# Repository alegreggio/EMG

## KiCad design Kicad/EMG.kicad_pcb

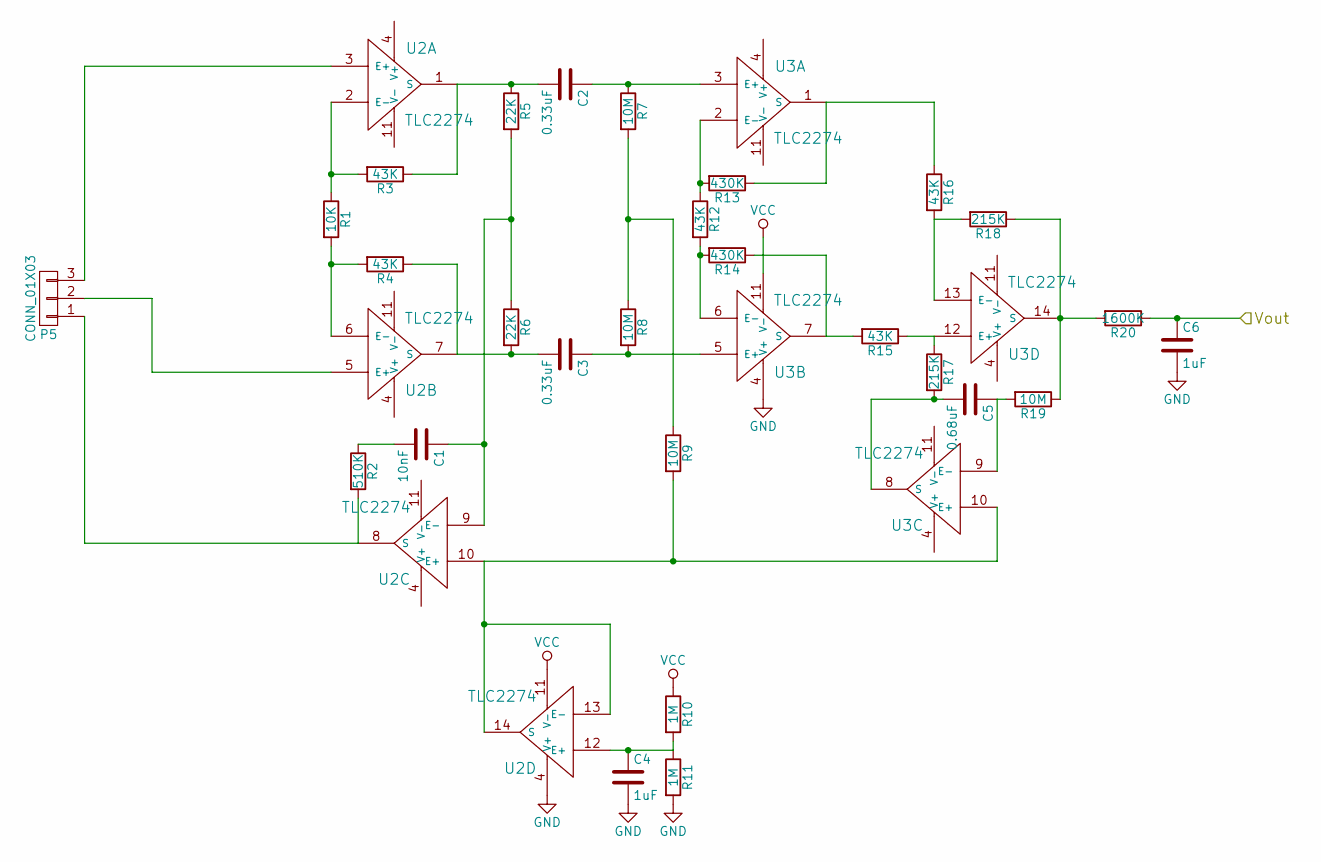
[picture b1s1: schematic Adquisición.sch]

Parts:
C1: 10nF; C_0603
C2, C3: 0.33uF; C_0603
C4, C6: 1uF; C_0603
C5: 0.68uF; C_0603
P5: CONN_01X03; Pin_Header_Straight_1x03_Pitch2.54mm
R1: 10K; R_0603
R2: 510K; R_0603
R3, R4, R12, R15, R16: 43K; R_0603
R5, R6: 22K; R_0603
R7, R8, R9, R19: 10M; R_0603
R10, R11: 1M; R_0603
R13, R14: 430K; R_0603
R17, R18: 215K; R_0603
R20: 1600K; R_0603
U2, U3: TLC2274; TSSOP-14_4.4x5mm_Pitch0.65mm

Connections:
/Microcontrolador/ADCin: C6.1, R20.1; also elsewhere on the board
unnamed: C1.1, R5.2, R6.1, U2.9 (E-)
unnamed: C1.2, R2.1
unnamed: C2.1, R7.1, U3.3 (E+)
unnamed: C2.2, R3.1, R5.1, U2.1 (S)
unnamed: C3.1, R8.2, U3.5 (E+)
unnamed: C3.2, R4.1, R6.2, U2.7 (S)
unnamed: C4.1, R10.2, R11.1, U2.12 (E+)
unnamed: C5.1, R19.2, U3.9 (E-)
unnamed: C5.2, R17.2, U3.8 (S)
unnamed: P5.1, R2.2, U2.8 (S)
unnamed: P5.2, U2.5 (E+)
unnamed: P5.3, U2.3 (E+)
unnamed: R1.1, R3.2, U2.2 (E-)
unnamed: R1.2, R4.2, U2.6 (E-)
unnamed: R7.2, R8.1, R9.1
unnamed: R9.2, U2.10 (E+), U2.13 (E-), U2.14 (S), U3.10 (E+)
unnamed: R12.1, R13.2, U3.2 (E-)
unnamed: R12.2, R14.2, U3.6 (E-)
unnamed: R13.1, R16.1, U3.1 (S)
unnamed: R14.1, R15.2, U3.7 (S)
unnamed: R15.1, R17.1, U3.12 (E+)
unnamed: R16.2, R18.2, U3.13 (E-)
unnamed: R18.1, R19.1, R20.2, U3.14 (S)

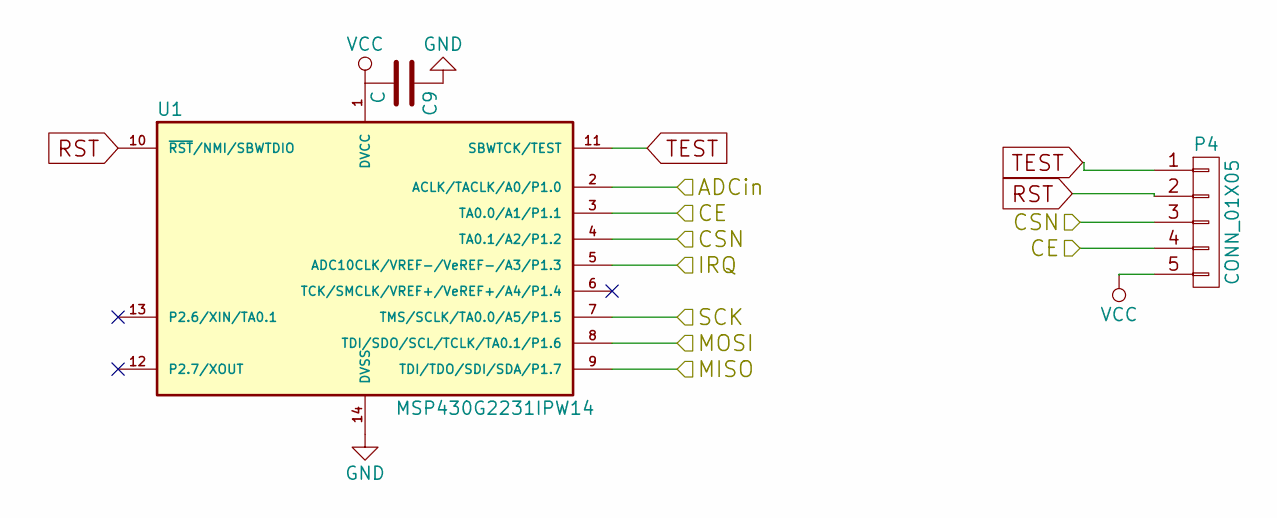
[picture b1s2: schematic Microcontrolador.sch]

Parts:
C9: C; C_0603
P4: CONN_01X05; Pin_Header_Straight_1x05_Pitch1.27mm
U1: MSP430G2231IPW14; TSSOP-14

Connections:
/Microcontrolador/ADCin: U1.2 (ACLK/TACLK/A0/P1.0); also elsewhere on the board
/Microcontrolador/CE: P4.4, U1.3 (TA0.0/A1/P1.1); also elsewhere on the board
/Microcontrolador/CSN: P4.3, U1.4 (TA0.1/A2/P1.2); also elsewhere on the board
/Microcontrolador/MISO: U1.9 (TDI/TDO/SDI/SDA/P1.7); also elsewhere on the board
/Microcontrolador/MOSI: U1.8 (TDI/SDO/SCL/TCLK/TA0.1/P1.6); also elsewhere on the board
/Microcontrolador/SCK: U1.7 (TMS/SCLK/TA0.0/A5/P1.5); also elsewhere on the board
RST: P4.2, U1.10 (~RST~/NMI/SBWTDIO)
TEST: P4.1, U1.11 (SBWTCK/TEST)

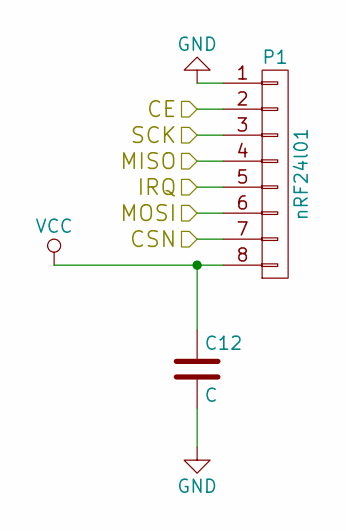
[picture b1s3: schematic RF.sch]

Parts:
C12: C; C_0603
P1: nRF24l01; nRF

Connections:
/Microcontrolador/CE: P1.3; also elsewhere on the board
/Microcontrolador/CSN: P1.4; also elsewhere on the board
/Microcontrolador/MISO: P1.7; also elsewhere on the board
/Microcontrolador/MOSI: P1.6; also elsewhere on the board
/Microcontrolador/SCK: P1.5; also elsewhere on the board

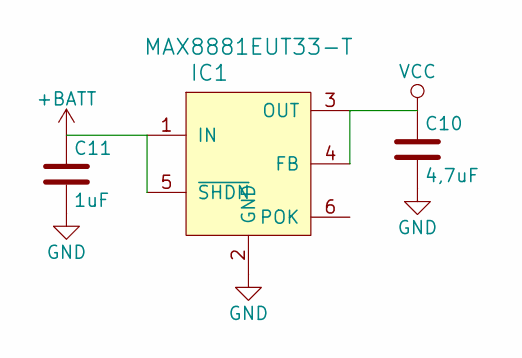
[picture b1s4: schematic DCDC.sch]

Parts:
C10: 4,7uF; C_0603
C11: 1uF; C_0603
IC1: MAX8881EUT33-T; sot23-6

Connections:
+BATT: C11.1, IC1.1 (IN), IC1.5 (~SHDN~); also elsewhere on the board

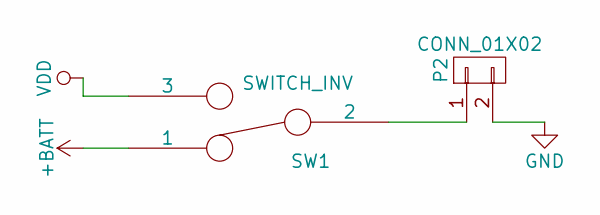
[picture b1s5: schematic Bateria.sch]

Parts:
P2: CONN_01X02; Pin_Header_Straight_1x02_Pitch1.27mm
SW1: SWITCH_INV; Pin_Header_Straight_1x03_Pitch1.27mm

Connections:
+BATT: SW1.1; also elsewhere on the board
unnamed: P2.1, SW1.2
VDD: SW1.3; also elsewhere on the board

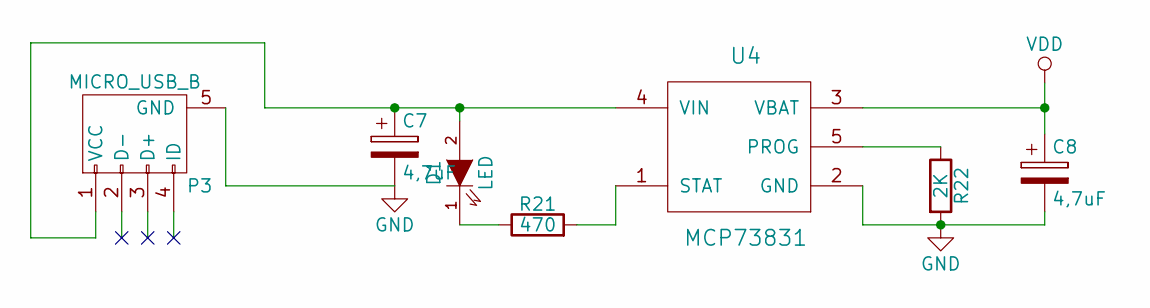
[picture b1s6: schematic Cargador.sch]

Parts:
C7, C8: 4,7uF; C_0603
D1: LED; Pin_Header_Straight_1x02_Pitch1.27mm
P3: MICRO_USB_B; usb_vert_2
R21: 470; R_0603
R22: 2K; R_0603
U4: MCP73831; sot23-5

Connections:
unnamed: C7.1, D1.2 (A), P3.1 (VCC), U4.4 (VIN)
unnamed: D1.1 (K), R21.1
unnamed: R21.2, U4.1 (STAT)
unnamed: R22.1, U4.5 (PROG)
VDD: C8.1, U4.3 (VBAT); also elsewhere on the board

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
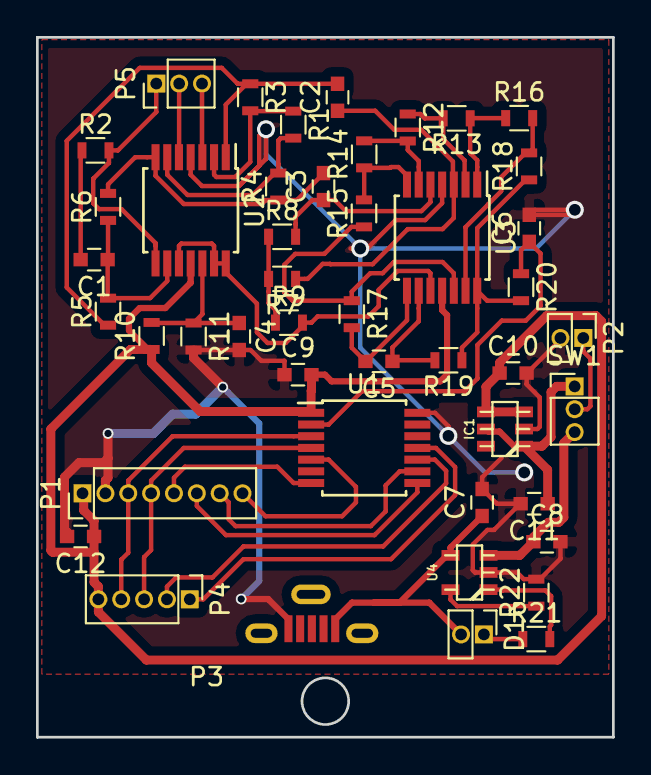
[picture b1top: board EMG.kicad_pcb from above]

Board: 2 copper layers, 32.0 x 38.9 mm, 46 parts (0 on the bottom side), 41 nets.

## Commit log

2016-08-25 Agregado todo el proyecto
2016-08-25 Agrego archivos al proyecto TX
2016-08-25 Agrego archivos al proyecto Transmisor
2016-08-25 cambios en nRF_init(), write() y read()
2016-08-26 Redefinimos las funciones write y read, y creamos la función set_status. Se redefinio la nRF_init.
2016-08-28 Se agregó la función set_dir y la rutina para configurar la dirección del TX. Se terminó la nRF_init.
2016-08-28 Creado proyecto RX
2016-08-28 Inicie el main
2016-08-28 Agregamos funciones enviar_dato, spi_transfer16 y la subrutina de interrupción del Timer0.
2016-08-29 Agragada spi_transfer16 y corrección de errores en build
2016-08-30 Agregada funcion flag_RX y corregida lógica del main
2016-08-30 Cambios del commit anterior debuggeado
2016-08-31 Agregué la rutina de interrución del P1.3, ademas de seleccionar el disparo por flanco descendiente. Activadas en el nRF las interuciones por TX_DS y MAX_RT en la fucnion nRF init. Terminada la funci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
2016-08-31 Cambios en funciones relacionadas con el registro STATUS
2016-09-02 Solucionado el problema de las interrupciones, desabilité la int de la USI. Las llamadas a int del timer y adc funcionan. Falta probar en conjunto con el RX para ver si funcionan la int del P1.3
2016-09-02 Solucionado el problema de pedido de int de la USI. Funciona todos los llamados a int. Funciona la funcion spi_transfer.
2016-09-09 Cambio correspondiente en funciones.c de RX
2016-09-11 Agregado componente OPA4243 y ubicación en esquemático
2016-09-11 Agregado de documentación
2016-09-12 Hojas de datos
2016-09-12 Actualización de la documentación
2016-09-12 Creada librería TLC2274
2016-09-17 Agregada librería power y actualizado esquemático con circuito de adquisición
2016-09-17 Pruebas varias.
2016-09-17 Cambié el LEd1 del P1.0 al P1.4. La entrada del ADC es el P1.0. El ADC está funcionado. No funciana la enviar_dato().
2016-09-17 División del esquemático en hojas jerárquicas y etapas de adquisición y transmisión completas.
2016-09-19 Hicimos el esquemático del cargador, y agregamos la hoja de datos
2016-09-19 Agregada librería del DC/DC (maxim)
2016-10-03 Prueba fallida transmisor-receptor. Compilación y debug correctos. - Cambio lógica de flag_RX por IF en main.c - Cambio en implementación de la función set_status en main.c como prueba (no sabemos si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
2016-10-06 Agregado componente DC/DC
2016-10-07 Comentadas las funciones de timer y adc, comentando todas las int el rograma funciona y parece que está enviando un valor fijo por RF.
2016-10-07 en la función enviar_dat se completó el payload, y se deshabilitó el AA de la data pipe 0.
2016-10-10 Cambio de archivo por estar corrupto
2016-10-10 Circuito de cargador modificado. A los demás les agregué capacitor en la alimentación, pines sin conexión y cambié BATT- por GND
2016-10-16 Configuración de USI (fase y polaridad). Eliminada transferencia completa de los 32 bytes (se definio payload como 2 bytes)
2016-10-16 Cambio en RX por la misma función config_USI implementada en TX
2016-10-16 Implementados delay y reset para inicializar el nRF24
2016-11-17 Cambiado delay de 5ms en funciones read_reg y write_reg
2016-11-17 Mismo cambio en TX
2016-11-20 Funciona la función enviar_dato. No estaba el CS habilitado antes de enviar el comando W_TX_PAYLOAD.
2016-11-20 Corrección de errores en RX. Comunicación exitosa
2016-11-20 Agregados footprints y 3D de SOT23-6. Asociado componente IC1
2016-11-21 Agregados los wrl y wings del amplificador y el cargador.
2016-11-21 Agregado wrl de TSSOP-14
2016-11-22 Agregados footprints de C_0805 y R_0805 y asociados a resistencias y capacitores del esquemático
2016-11-22 Asociado footprint de msp430
2016-11-22 Se agregó el ADC10, se envia por el módulo la temperatura interna del micro cada 0.5 seg.
2016-11-26 Se agregó el modo bajo consumo LPM3 con interrupción por TimerA. Se comentó la habilitación de la int de la USI.
2016-11-27 Después de mandar el pulso para enviar el paequete por rf, se entra en modo LPM3 hasta que ingresa la int por el P1.3.
2016-11-27 Agregada la interrupción del ADC, con modo LPM3
2016-11-30 Agregado switch en esquemático
2016-12-03 Se cambió el modo del ADC. Se utiliza el DTC, con 16 muestras. El adc toma las 16 muestras y el DTC las carga en memoria (se declaró el vec "adc"). Una vez que carga, se envía un paquete por el nRF d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
2016-12-03 Cambios en RX para recibir datos de 32 bytes
2017-02-17 Agregado jumpers para programar el micro
2017-02-17 Agregados footprints de pin headers para elementos faltantes (falta USB)
2017-02-18 Footprint del conector micro-usb vertical realizado.
2017-03-05 Se inició con el Pcb. Se eliminó el capacitor del socket del nrf. Se cambió el conector de la bat.
2017-03-05 Se agregó imagen del circuito nRF a la documentación
2017-03-09 Se incluyó nuevamente el C12.
2017-03-13 Se continua el pcb
2017-03-13 Ruteo de etapa de adquisición
2017-03-17 Reglas de diseño Mayer10mils
2017-03-17 Se creó la huella del nRF con los límites de la placa
2017-03-24 Versión unificada
2017-03-24 Cambios en tamaño de pinheaders
2017-03-27 Ruteo pcb
2017-03-27 Ruteo. Falta conectar GND
2017-03-27 Finalizada primera versión del pcb.
2017-03-31 Cambiado el switch por uno de punto medio. Aumento de ancho en pistas de alimentación. Plano de masa
2017-03-31 Modelo de header 1x8
2017-03-31 Asociado el modelo 3D del pin header 1x8
2017-03-31 Se creó el footprint usb_vert_2, y se cambió el pin out del usb en el esquema
2017-04-04 Se cambió el footprint del usb.
2017-04-07 Se añadió el agujero para tornillo. Diámetro de 1mm
2017-04-07 Se agregaron los 3d shapes de el cargador y dc/dc
2017-04-11 Cambiado el tamaño de las vías de conexión a tierra para que coincida con el de los pin headers (un solo taladro)
2017-04-11 Generados los Gerber y los archivos del taladro
2017-04-21 Se agrega la carpeta FreeCAD, con el archivo EMG que contiene a placa a partir del PCB Kicad
2017-04-21 Conexión de /SHDN a IN del DC/DC
2017-04-21 Se cambia la datasheet del usb. Se agrega los step y wrl del nrf.
2017-04-21 Se agrega los step y wrl del nrf.
2017-04-21 Se cambia el datasheet del usb
2017-04-21 Modelos 3D del USB
2017-04-21 Modificado modelo 3D del USB para que coincida con la placa.
2017-04-22 Se agregan los 3D shapes de los pin headers
2017-04-22 Se agregan los .step de los pin headers
2017-04-22 Se dejan solamente los .step de los pin headers.
2017-04-22 Generados archivos wrl a partir de los step
2017-04-23 Asociados los footprints con el modelo 3D de pinheader de dos y tres pines
2017-04-23 Pcb con componentes, faltan los pin headers de 1x8 y 1x5 y el nRF
2017-04-23 Prueba archivo step
2017-04-23 Se suben los archivos step y stl
2017-04-24 Se cambió el pin out de nRF en el esquemático y se hicieron las nuevas conexiones en el pcb.
2017-04-24 Generados nuevamente los gerber y enviados a fabricar
2017-05-05 Se cambió la huella del nrf.
2017-05-05 Actualizadas las huellas con los modelos 3D de los pin headers
2017-05-09 Creada la carpeta SolidWorks, con una versión del gabinete.
2017-05-09 Archivo solid a partir de el 3D de la placa
2017-05-09 Revert "Archivo solid a partir de el 3D de la placa"
    This reverts commit 48eafd460ad719d58312dd15356176066681b275.
2017-05-09 Agregado archivo solid a partir del 3D de la placa
2017-05-10 Se agrega una prueba de ensamblaje y se sigue trabajando con el gabinete.
2017-05-10 Modelo 3D de la batería
2017-05-12 Se agregaron los objetos bateria2, nRF y se comienza con el gabinete. Además, se realizaron los ensamblajes placa-nRF y al Prueba Ensamblaje se le agregó a bateria.
2017-05-12 Varios cambios en los 3DShapes.
2017-05-13 Se terminó la nueva versión del gabinete.
2017-05-13 Se realizó el ensamblaje con el segundo gabinete.
2017-05-19 Se agregó la pieza "Tapa"
2017-05-19 Se terminó la tapa y se agregó al ensamblaje2
2017-05-19 Link de switch en digikey
2017-05-19 Cambios en el ensamblaje 2
2017-06-02 Orificios para el led y los electrodos
2017-06-09 Creado proyecto para receptor con MSP430G2553, porque el 2231 no tiene UART
2017-06-16 Agregué dos scripts de python a la carpeta tools y los utilicé para leer la netlist y generar un listado de componentes, guardado como EMG.csv
2017-09-01 Agrego hoja de datos del msp430g22553
2017-09-01 Modelo 3D actualizado con ranura para el switch
2017-09-12 Se cambiaron nombres a las fuciones de la USCI. Se configuró el P1 como SPI.
2017-09-12 Confugurado el modo SPI en el USCI_B0, en la función conf_USCI_B0.
2017-09-22 Creado archivo gitignore para los proyectos de CCS. Debería ver sólo los cambios en los archivos del código fuente en cualquier proyecto
